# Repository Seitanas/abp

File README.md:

AntiBurglar-pi  
=====  
  
Home security system, based on raspberry-pi.  
System monitors two security zones, two temperature zones. Uses gnokii to send sms via gsm phone or modem, activates 
siren via relay.  
Also monitors status of powerline, reports if power is down.  
System control is done via SMS commands:  
  
<b>arm password</b> (e.g arm 1111) - system is armed instantly.  
<b>disarm password</b> - armed system deactivates after receiving SMS.  
<b>status password</b> - system responds with device uptime and temperature status after receiving SMS.  
<b>siren on password</b> - siren is turned on.  
<b>siren off password</b> - siren is turned off.  
  
When triggered, alarm warning is sent do a predefined number in config.h file.  
  
Edit src/config.h to fit your needs.  
You need to install libgnokii development libraries, also wiringpi:  
http://wiringpi.com/download-and-install/  
Make sure to create /etc/gnokii.conf config file with configuration for your GSM modem or phone.  
Example of working gnokii.conf file with "Huawei Technologies Co., Ltd. E220 HSDPA Modem / E230/E270/E870 HSDPA/HSUPA" modem:  
  
[global]  
model = AT  
port = /dev/ttyUSB0  
connection = serial  

To build and install system  
make  
make install  

If using raspbian distribution, copy init script from debian_init folder  
to /etc/init.d/ folder. 
Start antiburglar-pi with /etc/init.d/abp start  
  
More information about this project can be found at:  
http://www.neblogas.lt/2015/03/31/antiburglar-pi/  

v0.1c extended status report info.  
v0.1b some additional features.    
v0.1a some fixes, init scripts.  
v0.1 Initial release

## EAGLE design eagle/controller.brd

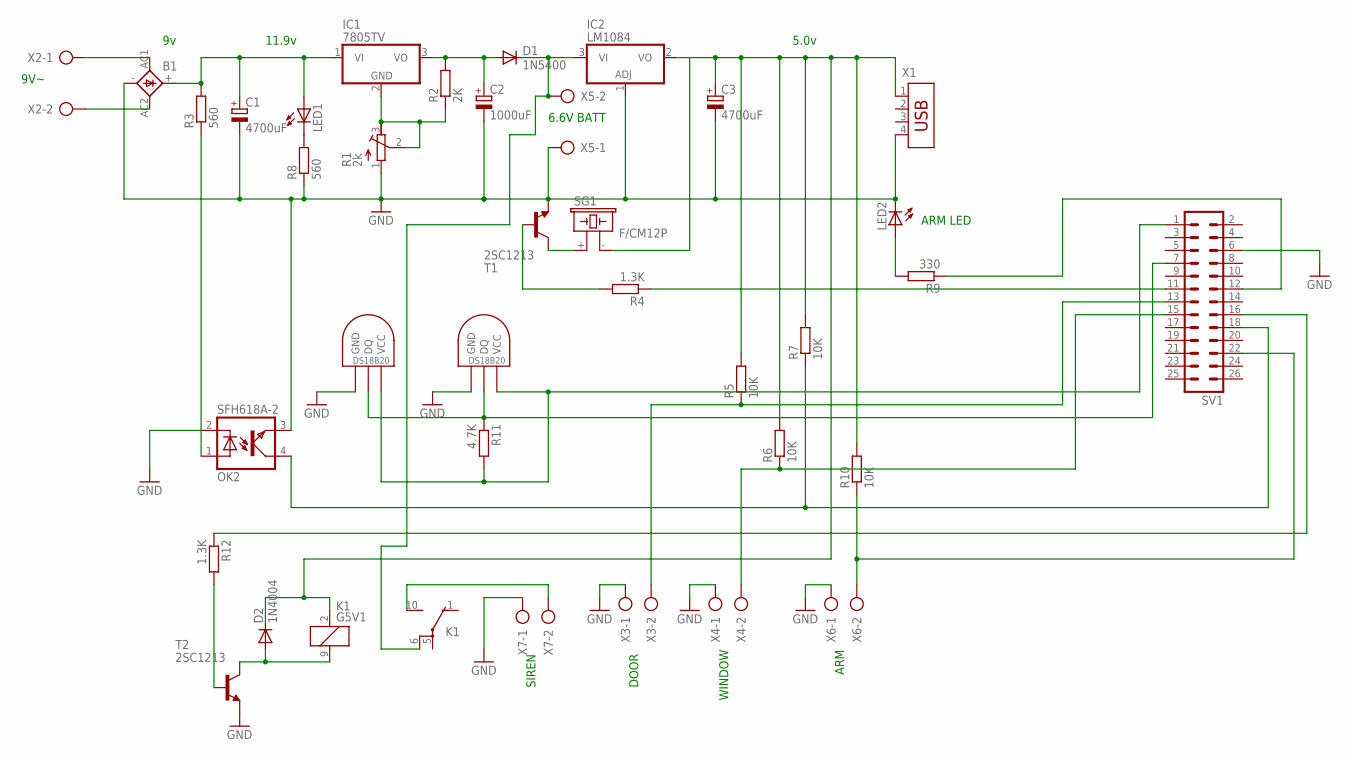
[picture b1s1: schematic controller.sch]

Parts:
B1: S41
C1, C3: 4700uF; E5-13
C2: 1000uF; E5-10,5
D1: 1N5400; DO201-15
D2: 1N4004; DO41-10
IC1: 7805TV; TO220V
IC2: LM1084; TO220V
K1: G5V1
LED1, LED2: LED5MM
OK2: SFH618A-2; DIP4
R1: 2k; RTRIM64W
R2: 2K; 0204/7
R3, R8: 560; 0204/7
R4, R12: 1.3K; 0204/7
R5, R6, R7, R10: 10K; 0204/7
R9: 330; 0204/7
R11: 4.7K; 0204/7
SG1: F/CM12P
SV1: ML26L
T1, T2: 2SC1213; TO92-EBC
U$1, U$2: DS1820TO92; DS1820
X1: USB-787616; USB
X2, X3, X4, X5, X6, X7: AK500/2

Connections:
GND: B1.-, C1.-, C2.-, C3.-, IC2.1 (ADJ), LED2.K (C), OK2.2 (C), OK2.3 (EMIT), R1.1 (E), R8.1, SV1.6, T1.E, T2.E, U$1.GND, U$2.GND, X1.4, X3.1, X4.1, X5.1, X6.1, X7.1
unnamed: IC1.2 (GND), R1.2 (S), R1.3 (A), R2.1
unnamed: R12.2, T2.B
unnamed: D2.A, K1.9 (2), T2.C
unnamed: C2.+, D1.A, IC1.3 (VO), R2.2
unnamed: B1.AC2, X2.2
unnamed: B1.AC1, X2.1
unnamed: B1.+, C1.+, IC1.1 (VI), LED1.A, R3.2
unnamed: OK2.1 (A), R3.1
unnamed: OK2.4 (COL), R7.1, SV1.18
unnamed: R4.2, T1.B
unnamed: R4.1, SV1.11
unnamed: SG1.+ (1), T1.C
unnamed: R5.1, SV1.13, X3.2
unnamed: LED1.K (C), R8.2
unnamed: R6.1, SV1.15, X4.2
unnamed: LED2.A, R9.2
unnamed: R9.1, SV1.12
unnamed: R10.1, SV1.22, X6.2
unnamed: R11.1, SV1.7, U$1.DQ, U$2.DQ
unnamed: R11.2, SV1.1, U$1.VDD (VCC), U$2.VDD (VCC)
unnamed: R12.1, SV1.16
unnamed: C3.+, D2.C, IC2.2 (VO), K1.2 (1), R5.2, R6.2, R7.2, R10.2, SG1.- (2), X1.1
unnamed: K1.10 (S), X7.2
unnamed: D1.C, IC2.3 (VI), K1.6, X5.2

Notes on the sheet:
5.0v
11.9v
DOOR
WINDOW
ARM
ARM LED
6.6V BATT
9V~
SIREN

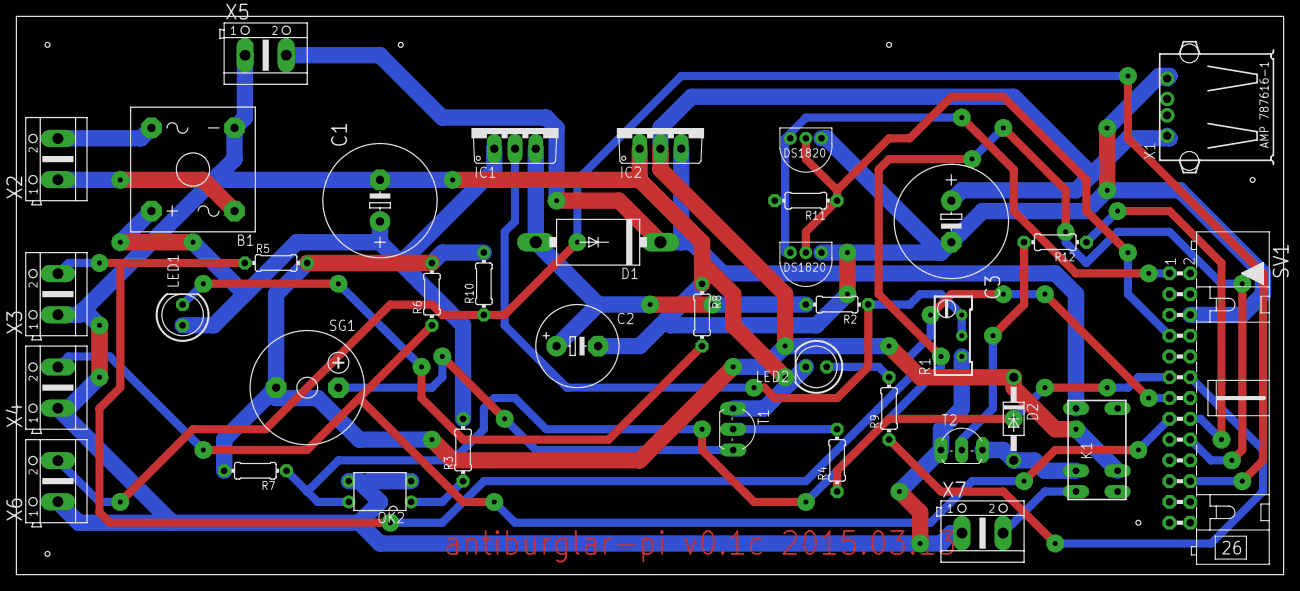
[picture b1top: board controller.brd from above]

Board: 2 copper layers, 154.9 x 68.2 mm, 37 parts (0 on the bottom side), 25 nets.

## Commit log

2015-03-26 v0.1a
2015-03-29 v0.1b
2015-04-22 Update main.c
    Bug with arming while door is open.
2015-05-01 v0.1c
2017-05-30 Create LICENSE
